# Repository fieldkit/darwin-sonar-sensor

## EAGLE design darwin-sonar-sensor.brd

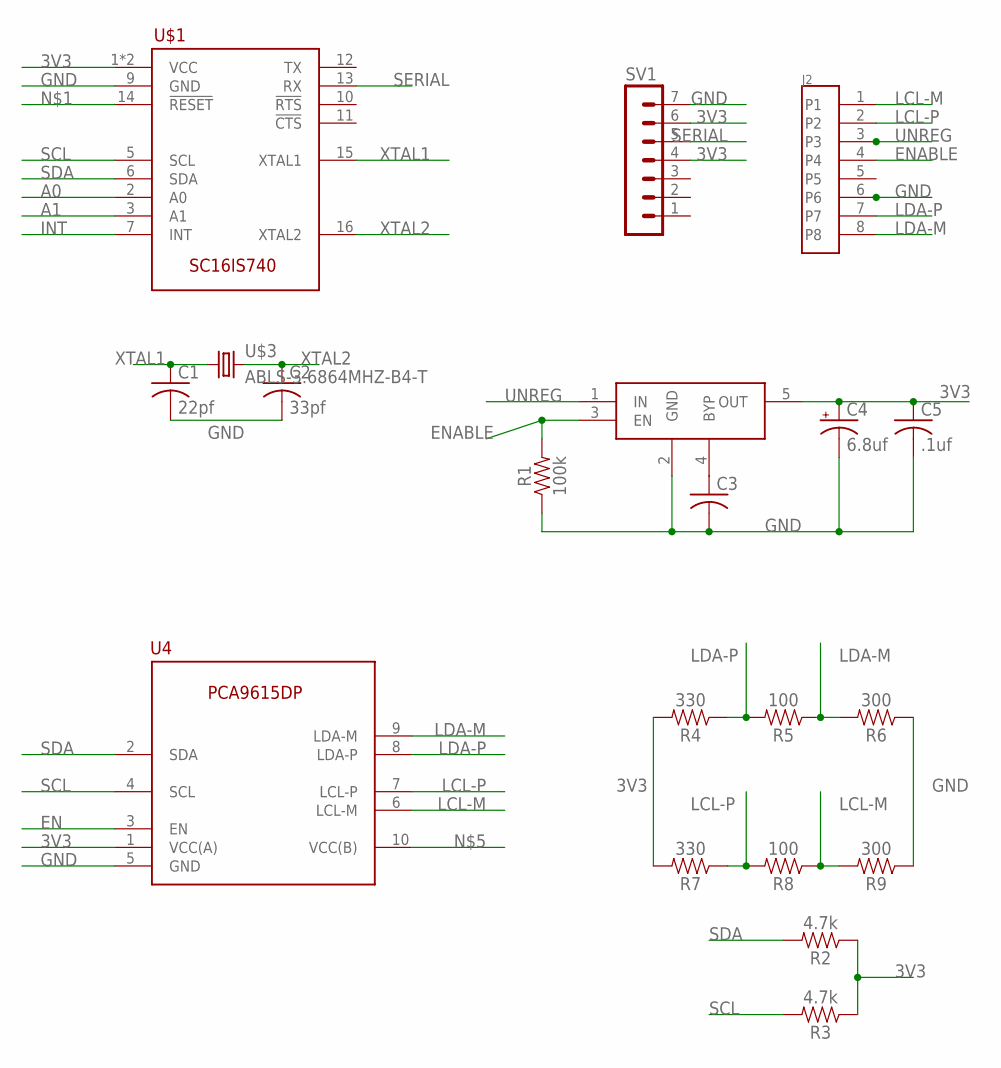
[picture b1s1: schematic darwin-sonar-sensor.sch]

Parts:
C1: 22pf; C0603K
C2: 33pf; C0603K
C3: C-USC0603K; C0603K
C4: 6.8uf; A/3216-18R
C5: .1uf; C0603K
J2: 95501-6889VERT; 85513-5009
R1: 100k; 0603
R2, R3: 4.7k; 0603
R4, R7: 330; 0603
R5, R8: 100; 0603
R6, R9: 300; 0603
SV1: MA07-1
U4: PCA9615; SOP50P490X110-10
U$1: SC16IS740; SOP65P640X110-16
U$3: ABLS-3.6864MHZ-B4-T; ABLS
U$4: MIC5219-3.3YM5-TR; SOT95P280X145-5

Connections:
3V3: C4.+, C5.1, R2.1, R3.1, R4.2, R7.2, SV1.4, SV1.6, U4.1 (VCC(A)), U$1.1 (VCC), U$1.8 (VCC), U$4.5 (OUT)
A0: U$1.2 (A0)
A1: U$1.3 (A1)
EN: U4.3 (EN)
ENABLE: J2.4, R1.2, U$4.3 (EN)
GND: C1.2, C2.2, C3.2, C4.-, C5.2, J2.6, R1.1, R6.1, R9.1, SV1.7, U4.5 (GND), U$1.9 (GND), U$4.2 (GND)
INT: U$1.7 (INT)
LCL-M: J2.1, R8.1, R9.2, U4.6 (LCL-M)
LCL-P: J2.2, R7.1, R8.2, U4.7 (LCL-P)
LDA-M: J2.8, R5.1, R6.2, U4.9 (LDA-M)
LDA-P: J2.7, R4.1, R5.2, U4.8 (LDA-P)
unnamed: C3.1, U$4.4 (BYP)
SCL: R3.2, U4.4 (SCL), U$1.5 (SCL)
SDA: R2.2, U4.2 (SDA), U$1.6 (SDA)
SERIAL: SV1.5, U$1.13 (RX)
UNREG: J2.3, U$4.1 (IN)
XTAL1: C1.1, U$1.15 (XTAL1), U$3.P$1 (1)
XTAL2: C2.1, U$1.16 (XTAL2), U$3.P$2 (2)

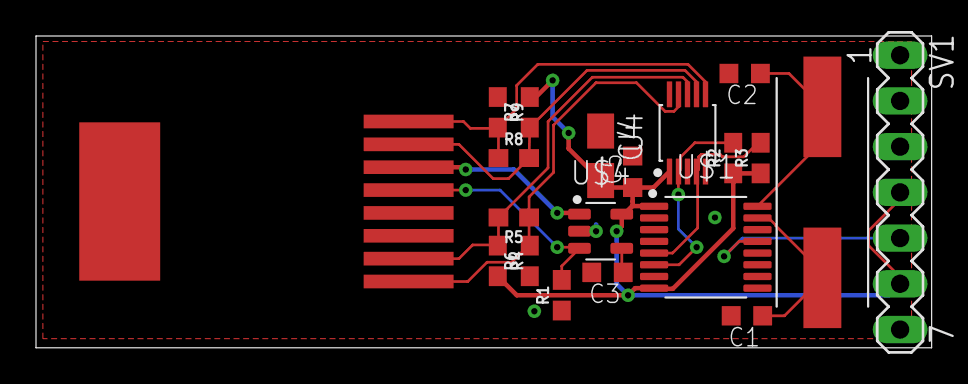
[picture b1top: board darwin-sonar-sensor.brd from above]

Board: 2 copper layers, 49.8 x 17.3 mm, 20 parts (0 on the bottom side), 14 nets.

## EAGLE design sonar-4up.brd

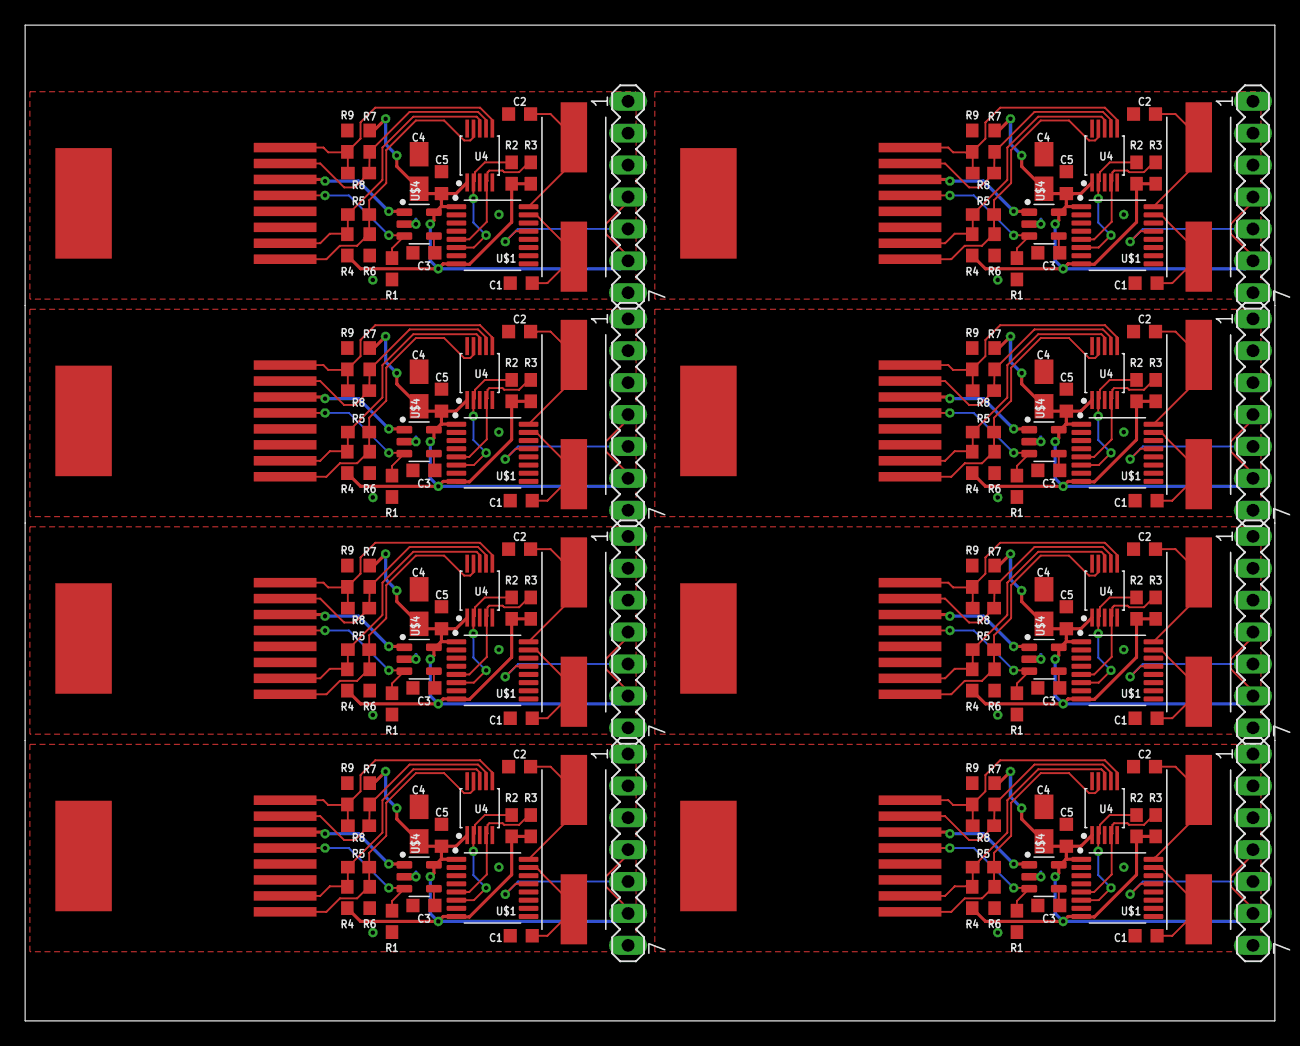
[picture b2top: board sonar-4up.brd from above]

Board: 2 copper layers, 99.5 x 79.3 mm, 160 parts (0 on the bottom side), 112 nets.

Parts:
C1, C6, C11, C16, C21, C26, C31, C36: 22pf; C0603K
C2, C7, C12, C17, C22, C27, C32, C37: 33pf; C0603K
C3, C8, C13, C18, C23, C28, C33, C38: C0603K
C4, C9, C14, C19, C24, C29, C34, C39: 6.8uf; A/3216-18R
C5, C10, C15, C20, C25, C30, C35, C40: .1uf; C0603K
J1, J2, J3, J4, J5, J6, J7, J8: 95501-6889VERT; 85513-5009
R1, R10, R19, R28, R37, R46, R55, R64: 100k; 0603
R2, R3, R11, R12, R20, R21, R29, R30, R38, R39, R47, R48, R56, R57, R65, R66: 4.7k; 0603
R4, R7, R13, R16, R22, R25, R31, R34, R40, R43, R49, R52, R58, R61, R67, R70: 330; 0603
R5, R8, R14, R17, R23, R26, R32, R35, R41, R44, R50, R53, R59, R62, R68, R71: 100; 0603
R6, R9, R15, R18, R24, R27, R33, R36, R42, R45, R51, R54, R60, R63, R69, R72: 300; 0603
SV1, SV2, SV3, SV4, SV5, SV6, SV7, SV8: MA07-1
U1, U2, U3, U4, U5, U6, U7, U8: PCA9615; SOP50P490X110-10
U$1, U$2, U$7, U$10, U$13, U$16, U$19, U$22: SC16IS740; SOP65P640X110-16
U$3, U$5, U$8, U$11, U$14, U$17, U$20, U$23: ABLS-3.6864MHZ-B4-T; ABLS
U$4, U$6, U$9, U$12, U$15, U$18, U$21, U$24: MIC5219-3.3YM5-TR; SOT95P280X145-5

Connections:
3V1: C9.+, C10.1, R11.1, R12.1, R13.2, R16.2, SV2.4, SV2.6, U1.1, U$2.1, U$2.8, U$6.5
3V2: C14.+, C15.1, R20.1, R21.1, R22.2, R25.2, SV3.4, SV3.6, U2.1, U$7.1, U$7.8, U$9.5
3V3: C4.+, C5.1, R2.1, R3.1, R4.2, R7.2, SV1.4, SV1.6, U4.1, U$1.1, U$1.8, U$4.5
3V4: C19.+, C20.1, R29.1, R30.1, R31.2, R34.2, SV4.4, SV4.6, U3.1, U$10.1, U$10.8, U$12.5
3V5: C24.+, C25.1, R38.1, R39.1, R40.2, R43.2, SV5.4, SV5.6, U5.1, U$13.1, U$13.8, U$15.5
3V6: C29.+, C30.1, R47.1, R48.1, R49.2, R52.2, SV6.4, SV6.6, U6.1, U$16.1, U$16.8, U$18.5
3V7: C34.+, C35.1, R56.1, R57.1, R58.2, R61.2, SV7.4, SV7.6, U7.1, U$19.1, U$19.8, U$21.5
3V8: C39.+, C40.1, R65.1, R66.1, R67.2, R70.2, SV8.4, SV8.6, U8.1, U$22.1, U$22.8, U$24.5
ENABLE: J2.4, R1.2, U$4.3
ENABLE1: J1.4, R10.2, U$6.3
ENABLE2: J3.4, R19.2, U$9.3
ENABLE3: J4.4, R28.2, U$12.3
ENABLE4: J5.4, R37.2, U$15.3
ENABLE5: J6.4, R46.2, U$18.3
ENABLE6: J7.4, R55.2, U$21.3
ENABLE7: J8.4, R64.2, U$24.3
GND: C1.2, C2.2, C3.2, C4.-, C5.2, J2.6, R1.1, R6.1, R9.1, SV1.7, U4.5, U$1.9, U$4.2
GND1: C6.2, C7.2, C8.2, C9.-, C10.2, J1.6, R10.1, R15.1, R18.1, SV2.7, U1.5, U$2.9, U$6.2
GND2: C11.2, C12.2, C13.2, C14.-, C15.2, J3.6, R19.1, R24.1, R27.1, SV3.7, U2.5, U$7.9, U$9.2
GND3: C16.2, C17.2, C18.2, C19.-, C20.2, J4.6, R28.1, R33.1, R36.1, SV4.7, U3.5, U$10.9, U$12.2
GND4: C21.2, C22.2, C23.2, C24.-, C25.2, J5.6, R37.1, R42.1, R45.1, SV5.7, U5.5, U$13.9, U$15.2
GND5: C26.2, C27.2, C28.2, C29.-, C30.2, J6.6, R46.1, R51.1, R54.1, SV6.7, U6.5, U$16.9, U$18.2
GND6: C31.2, C32.2, C33.2, C34.-, C35.2, J7.6, R55.1, R60.1, R63.1, SV7.7, U7.5, U$19.9, U$21.2
GND7: C36.2, C37.2, C38.2, C39.-, C40.2, J8.6, R64.1, R69.1, R72.1, SV8.7, U8.5, U$22.9, U$24.2
LCL-M: J2.1, R8.1, R9.2, U4.6
LCL-M1: J1.1, R17.1, R18.2, U1.6
LCL-M2: J3.1, R26.1, R27.2, U2.6
LCL-M3: J4.1, R35.1, R36.2, U3.6
LCL-M4: J5.1, R44.1, R45.2, U5.6
LCL-M5: J6.1, R53.1, R54.2, U6.6
LCL-M6: J7.1, R62.1, R63.2, U7.6
LCL-M7: J8.1, R71.1, R72.2, U8.6
LCL-P: J2.2, R7.1, R8.2, U4.7
LCL-P1: J1.2, R16.1, R17.2, U1.7
LCL-P2: J3.2, R25.1, R26.2, U2.7
LCL-P3: J4.2, R34.1, R35.2, U3.7
LCL-P4: J5.2, R43.1, R44.2, U5.7
LCL-P5: J6.2, R52.1, R53.2, U6.7
LCL-P6: J7.2, R61.1, R62.2, U7.7
LCL-P7: J8.2, R70.1, R71.2, U8.7
LDA-M: J2.8, R5.1, R6.2, U4.9
LDA-M1: J1.8, R14.1, R15.2, U1.9
LDA-M2: J3.8, R23.1, R24.2, U2.9
LDA-M3: J4.8, R32.1, R33.2, U3.9
LDA-M4: J5.8, R41.1, R42.2, U5.9
LDA-M5: J6.8, R50.1, R51.2, U6.9
LDA-M6: J7.8, R59.1, R60.2, U7.9
LDA-M7: J8.8, R68.1, R69.2, U8.9
LDA-P: J2.7, R4.1, R5.2, U4.8
LDA-P1: J1.7, R13.1, R14.2, U1.8
LDA-P2: J3.7, R22.1, R23.2, U2.8
LDA-P3: J4.7, R31.1, R32.2, U3.8
LDA-P4: J5.7, R40.1, R41.2, U5.8
LDA-P5: J6.7, R49.1, R50.2, U6.8
LDA-P6: J7.7, R58.1, R59.2, U7.8
LDA-P7: J8.7, R67.1, R68.2, U8.8
unnamed: C3.1, U$4.4
unnamed: C8.1, U$6.4
unnamed: C13.1, U$9.4
unnamed: C18.1, U$12.4
unnamed: C23.1, U$15.4
unnamed: C28.1, U$18.4
unnamed: C33.1, U$21.4
unnamed: C38.1, U$24.4
SCL: R3.2, U4.4, U$1.5
SCL1: R12.2, U1.4, U$2.5
SCL2: R21.2, U2.4, U$7.5
SCL3: R30.2, U3.4, U$10.5
SCL4: R39.2, U5.4, U$13.5
SCL5: R48.2, U6.4, U$16.5
SCL6: R57.2, U7.4, U$19.5
SCL7: R66.2, U8.4, U$22.5
SDA: R2.2, U4.2, U$1.6
SDA1: R11.2, U1.2, U$2.6
SDA2: R20.2, U2.2, U$7.6
SDA3: R29.2, U3.2, U$10.6
SDA4: R38.2, U5.2, U$13.6
SDA5: R47.2, U6.2, U$16.6
SDA6: R56.2, U7.2, U$19.6
SDA7: R65.2, U8.2, U$22.6
SERIAL: SV1.5, U$1.13
SERIAL1: SV2.5, U$2.13
SERIAL2: SV3.5, U$7.13
SERIAL3: SV4.5, U$10.13
SERIAL4: SV5.5, U$13.13
SERIAL5: SV6.5, U$16.13
SERIAL6: SV7.5, U$19.13
SERIAL7: SV8.5, U$22.13
UNREG: J2.3, U$4.1
UNREG1: J1.3, U$6.1
UNREG2: J3.3, U$9.1
UNREG3: J4.3, U$12.1
UNREG4: J5.3, U$15.1
UNREG5: J6.3, U$18.1
UNREG6: J7.3, U$21.1
UNREG7: J8.3, U$24.1
XTAL1: C1.1, U$1.15, U$3.P$1
XTAL2: C2.1, U$1.16, U$3.P$2
XTAL3: C6.1, U$2.15, U$5.P$1
XTAL4: C7.1, U$2.16, U$5.P$2
XTAL5: C11.1, U$7.15, U$8.P$1
XTAL6: C12.1, U$7.16, U$8.P$2
XTAL7: C16.1, U$10.15, U$11.P$1
XTAL8: C17.1, U$10.16, U$11.P$2
XTAL9: C21.1, U$13.15, U$14.P$1
XTAL10: C22.1, U$13.16, U$14.P$2
XTAL11: C26.1, U$16.15, U$17.P$1
XTAL12: C27.1, U$16.16, U$17.P$2
XTAL13: C31.1, U$19.15, U$20.P$1
XTAL14: C32.1, U$19.16, U$20.P$2
XTAL15: C36.1, U$22.15, U$23.P$1
XTAL16: C37.1, U$22.16, U$23.P$2

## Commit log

2020-02-11 New Panel

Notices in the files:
parts and their libraries:
SparkFun-Resistors: Licensing: Creative Commons ShareAlike 4.0 International - https://creativecommons.org/licenses/by-sa/4.0
